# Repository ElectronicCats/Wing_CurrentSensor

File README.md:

# Wing Current Sensor

## License
Electronic Cats invests time and resources providing this open source design, please support Electronic Cats and open-source hardware by purchasing products from Electronic Cats!

Designed by Electronic Cats.

Firmware released under an GNU AGPL v3.0 license. See the LICENSE file for more information.

Hardware released under an CERN Open Hardware Licence v1.2. See the LICENSE_HARDWARE file for more information.

Electronic Cats is a registered trademark, please do not use if you sell these PCBs.

March 2021

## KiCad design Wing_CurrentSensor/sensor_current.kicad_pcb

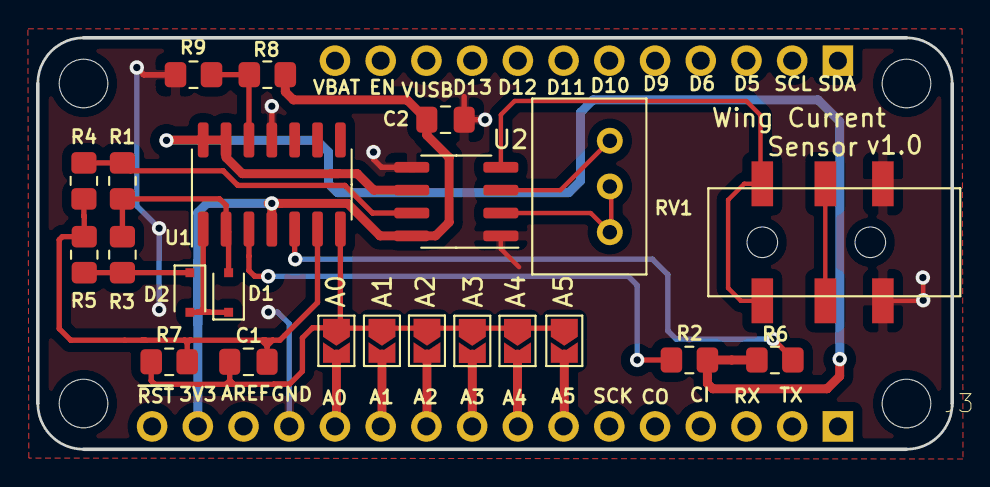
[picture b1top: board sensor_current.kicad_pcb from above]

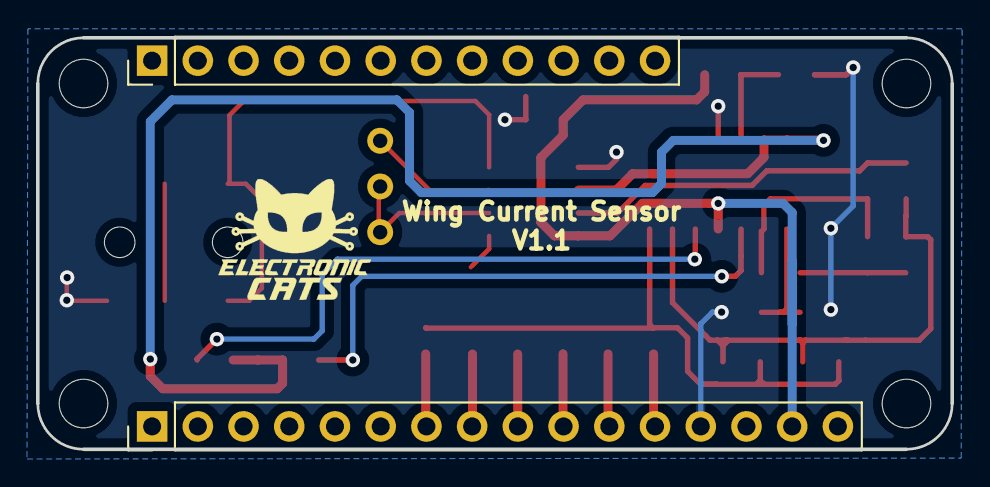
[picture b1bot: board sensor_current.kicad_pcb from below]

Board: 2 copper layers, 50.8 x 22.9 mm, 25 parts (2 on the bottom side), 21 nets.

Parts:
A0: A0; SolderJumper-2_P1.3mm_Open_TrianglePad1.0x1.5mm
A1: A1; SolderJumper-2_P1.3mm_Open_TrianglePad1.0x1.5mm
A2: A2; SolderJumper-2_P1.3mm_Open_TrianglePad1.0x1.5mm
A3: A3; SolderJumper-2_P1.3mm_Open_TrianglePad1.0x1.5mm
A4: A4; SolderJumper-2_P1.3mm_Open_TrianglePad1.0x1.5mm
A5: A5; SolderJumper-2_P1.3mm_Open_TrianglePad1.0x1.5mm
C1: 10 μ; C_0805_2012Metric_Pad1.18x1.45mm_HandSolder
C2: 0.1μ; C_0805_2012Metric_Pad1.18x1.45mm_HandSolder
D1, D2: DIODE; D_SOD-323F
J1: feather long; PinHeader_1x16_P2.54mm_Vertical
J2: feather short; PinHeader_1x12_P2.54mm_Vertical
J3: PJ-320B; CUI_SJ-3524-SMT
R1, R3, R4, R7, R8, R9: 10K; R_0805_2012Metric_Pad1.20x1.40mm_HandSolder
R2, R5: 5K; R_0805_2012Metric_Pad1.20x1.40mm_HandSolder
R6: 3.3K; R_0805_2012Metric_Pad1.20x1.40mm_HandSolder
RV1: 10K; Potentiometer_Bourns_3299W_Vertical
U1: TL084; SO-14_3.9x8.65mm_P1.27mm
U2: AD8226; SOIC-8_3.9x4.9mm_P1.27mm

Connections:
+3V3: C2.1, J1.15, R8.1, U1.4, U2.8
/A0: A0.2, J1.12
/A1: A1.2, J1.11
/A2: A2.2, J1.10
/A3: A3.2, J1.9
/A4: A4.2, J1.8
/A5: A5.2, J1.7
/IN+: J3.3, U2.4
/OUT: A0.1, A1.1, A2.1, A3.1, A4.1, A5.1, C1.1, R7.1, U1.7
/OUT1: R1.1, R4.1, U2.7
/VREF: R2.2, R6.2, U1.13, U1.14, U2.6
GND: C2.2, J1.13, J3.1, R9.2, U1.11, U2.1, U2.5
unnamed: C1.2, R4.2, R5.2, R7.2, U1.6
unnamed: D1.1, D2.2, U1.1
unnamed: D1.2, R1.2, R3.1, U1.2
unnamed: D2.1, R3.2, R5.1
unnamed: R2.1, U1.3
unnamed: R6.1, U1.5
unnamed: R8.2, R9.1, U1.12
unnamed: RV1.1, RV1.2, U2.2
unnamed: RV1.3, U2.3

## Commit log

2021-01-12 Add_folder
2021-01-21 update schematic
2021-01-28 PCB
    28/01/21
2021-01-29 I deleted the previous folder
2021-02-01 Update PCB
    The space was better used and the pdf of the plate was created
2021-02-12 I put only one folder instead 2
    schematic updated
2021-02-12 AD8226 eliminated
    auto_awesome
    Se muestra la traducción de se reemplazo el AD8226 por un modulo del TL084, ademas se cambio el orden de los modulos, siendo estos el modulo B,C y D, se realizo nuevo esquematico y nueva PCB del circ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
    Traducir se remplazo el AD8226 por un modulo del TL084, ademas se cambio el orden de los modulos, siendo estos el modulo B,C y D, se realizo nuevo esquematico y nueva PCB del circuito
    174 / 5000
    Resultados de traducción
    The AD8226 was replaced by a TL084 module, also the order of the modules was changed, these being module B, C and D, a new schematic and new circuit PCB was made
2021-02-12 Printable Plate PDF
    I just add the PDF
2021-02-12 11/02/2021
    document removed
2021-02-12 AD8226 eliminated
    The AD8226 was replaced by a TL084 module, also the order of the modules was changed, these being module B, C and D, a new schematic and new circuit PCB was made
2021-02-23 Printable of PCB without AD8226
2021-02-24 Wing current sensor 1.0
    1rst version of the PCB ad8226 and TL084
2021-02-24 Wing_current_1.0
2021-02-24 1.1 version
    second pcb was added
2021-02-25 Wing_current_1.2
    The new version of the first pcb was added
2021-02-26 error fixed
    missing conection detected and eliminated
2021-03-03 1.2.1
    missing network detected and fixed
2021-03-03 pcb on wing format
    The previous circuit has been included in wing format
    missing jack stereo footprint
2021-03-04 PCB with correct jack added
    The correct footprint and icon was added and the second PCB was made
2021-03-05 Manual version
    1rst version of the PCB ad8226 and TL084
2021-03-05 test txt
2021-03-05 remove AD8226
    second pcb was added
2021-03-05 TL084 divisor
    missing network detected and fixed
2021-03-05 update files
2021-03-09 Jack swapped and update of labels
2021-03-12 power at 3.3v and labels update
2021-03-12 add logos
2021-03-12 update connecotr for jumpers
2021-03-12 update traces
2021-06-22 Add_Connector
2021-06-22 Change_BOM
2021-07-20 Change_name_add connector
2021-07-20 Add_labels
2021-07-21 Add_3D_Models_Add_Diode
2021-07-21 Init_BOM_Change3D_Model
2021-07-22 Finish_BOM
2021-07-26 Connect_resistor
2021-07-26 Move_Labels
